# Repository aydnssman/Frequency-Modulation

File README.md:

# Frequency-Modulation
Schematic and PCB were drawn using Autodesk Eagle software. The whole system has been tested and working.

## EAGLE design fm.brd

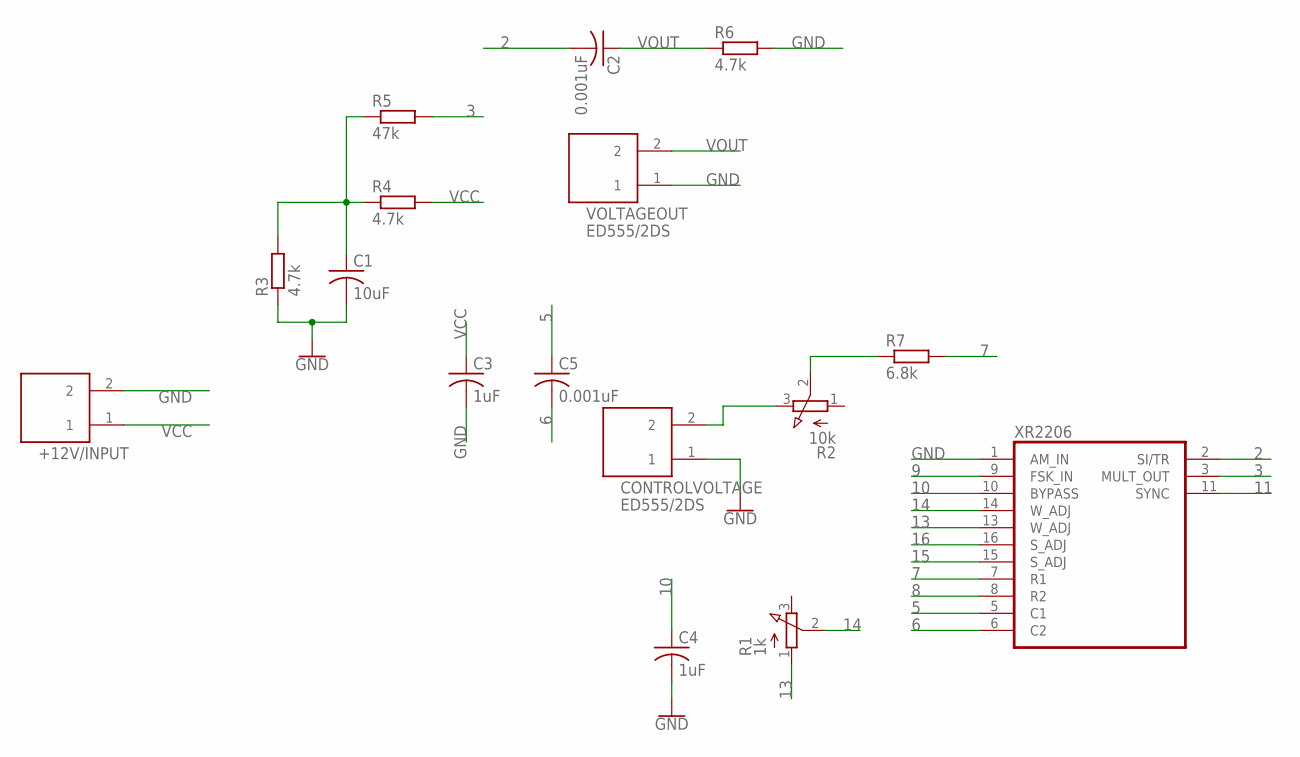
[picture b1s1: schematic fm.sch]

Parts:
+12V/INPUT: ED555/2DS
C1: 10uF; C050-030X075
C2, C5: 0.001uF; C050-030X075
C3, C4: 1uF; C050-030X075
CONTROLVOLTAGE: ED555/2DS
R1: 1k; 3RP/1610N
R2: 10k; 3RP/1610N
R3, R4, R6: 4.7k; 0207/10
R5: 47k; 0207/10
R7: 6.8k; 0207/10
VOLTAGEOUT: ED555/2DS
XR2206: XR-2206; DIL16

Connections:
2: C2.2, XR2206.2 (SI/TR)
3: R5.2, XR2206.3 (MULT_OUT)
5: C5.1, XR2206.5 (C1)
6: C5.2, XR2206.6 (C2)
7: R7.2, XR2206.7 (R1)
8: XR2206.8 (R2)
9: XR2206.9 (FSK_IN)
10: C4.1, XR2206.10 (BYPASS)
11: XR2206.11 (SYNC)
13: R1.1 (A), XR2206.13 (W_ADJ)
14: R1.2 (S), XR2206.14 (W_ADJ)
15: XR2206.15 (S_ADJ)
16: XR2206.16 (S_ADJ)
GND: +12V/INPUT.2, C1.2, C3.2, C4.2, CONTROLVOLTAGE.1, R3.1, R6.2, VOLTAGEOUT.1, XR2206.1 (AM_IN), XR2206.12 (GND)
unnamed: C1.1, R3.2, R4.1, R5.1
unnamed: R2.2 (S), R7.1
unnamed: CONTROLVOLTAGE.2, R2.3 (E)
VCC: +12V/INPUT.1, C3.1, R4.2, XR2206.4 (VCC)
VOUT: C2.1, R6.1, VOLTAGEOUT.2

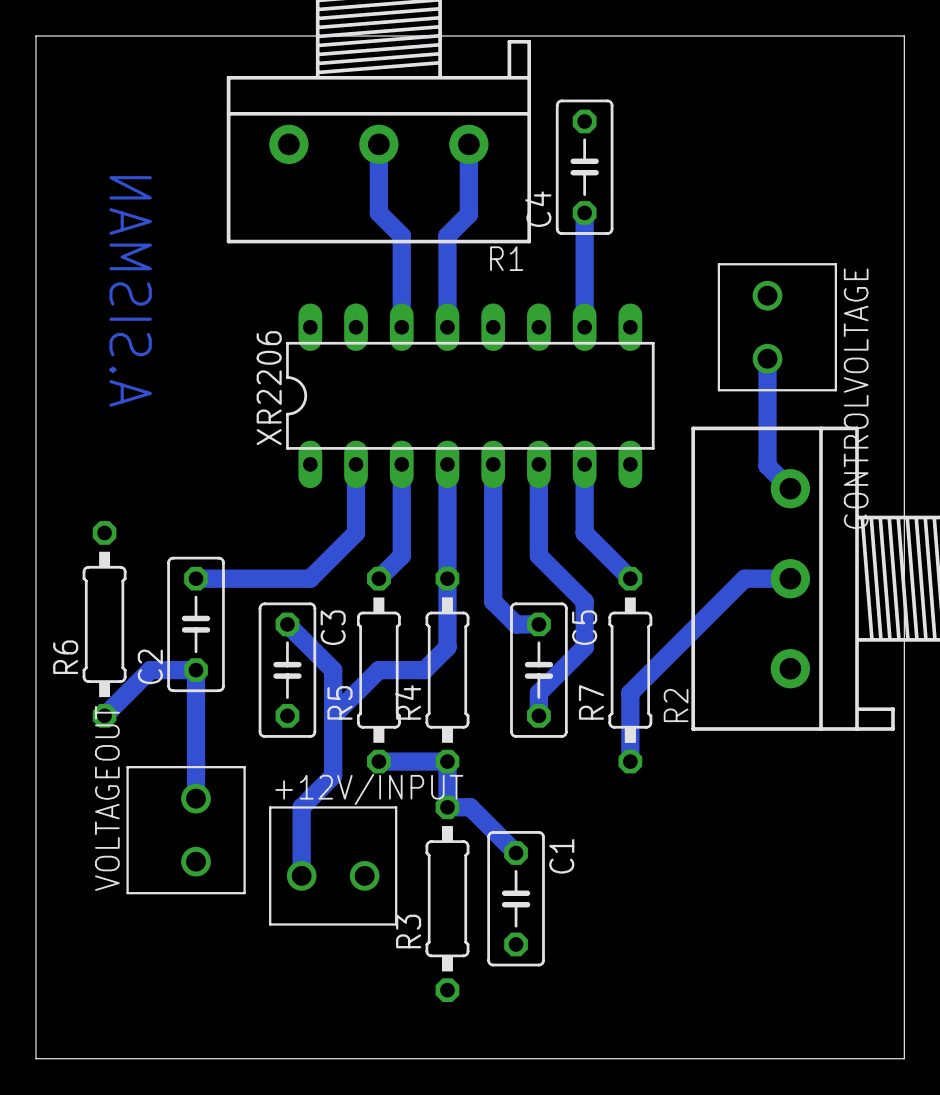
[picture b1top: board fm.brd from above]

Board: 2 copper layers, 48.2 x 56.8 mm, 16 parts (0 on the bottom side), 14 nets.

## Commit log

2019-12-16 Frequency Modulation

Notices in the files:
parts and their libraries:
SparkFun-PowerSymbols: Licensing: Creative Commons ShareAlike 4.0 International - https://creativecommons.org/licenses/by-sa/4.0
